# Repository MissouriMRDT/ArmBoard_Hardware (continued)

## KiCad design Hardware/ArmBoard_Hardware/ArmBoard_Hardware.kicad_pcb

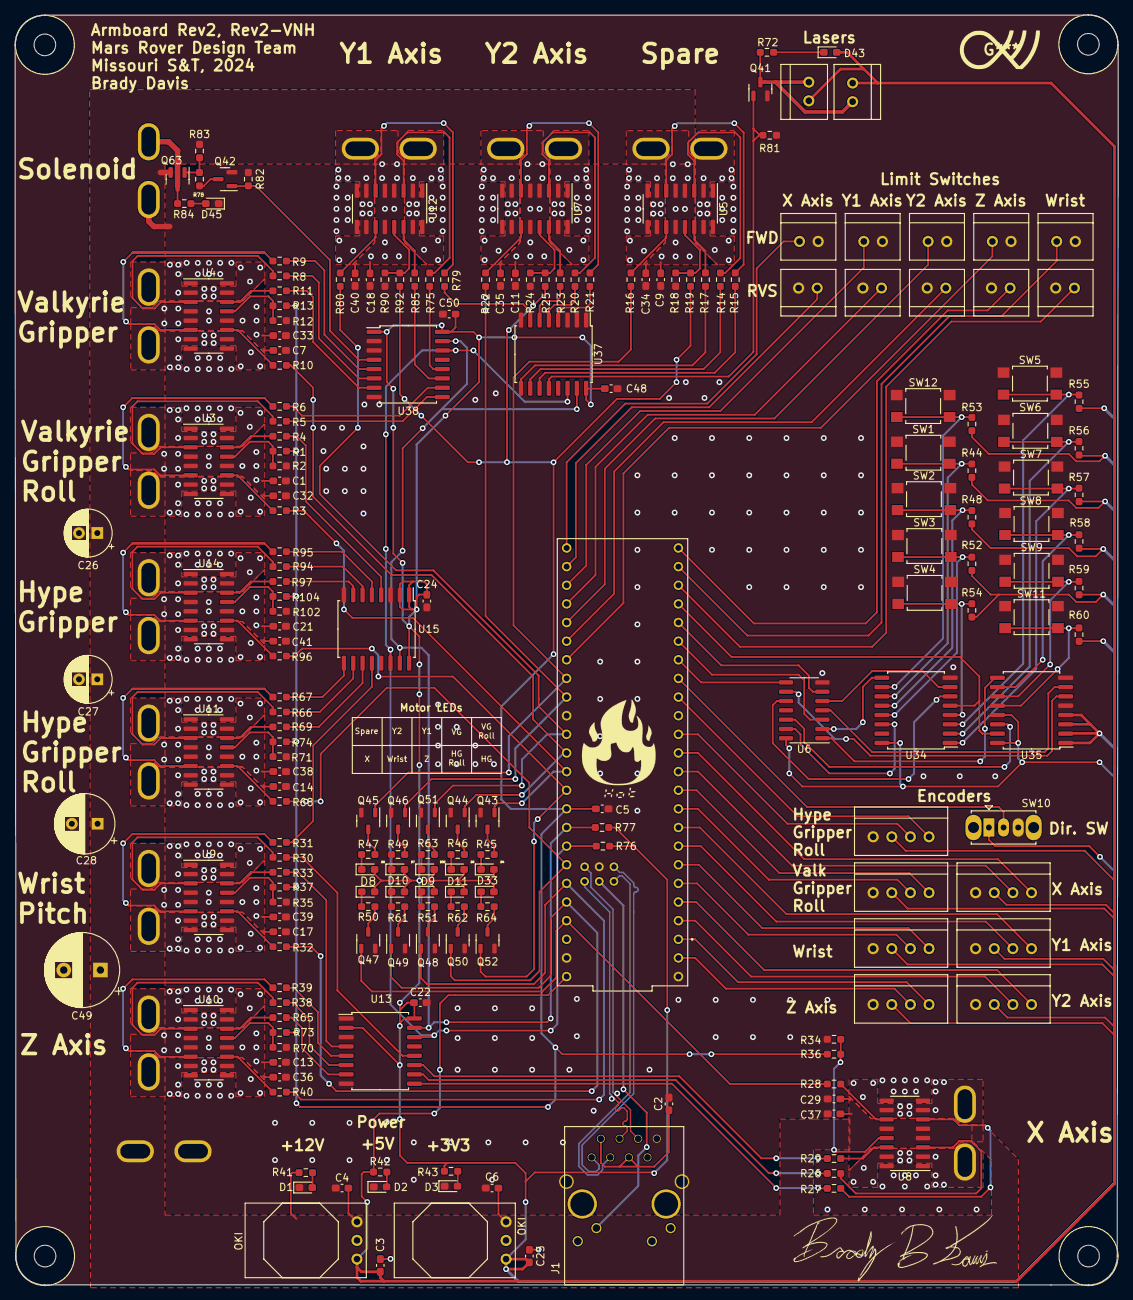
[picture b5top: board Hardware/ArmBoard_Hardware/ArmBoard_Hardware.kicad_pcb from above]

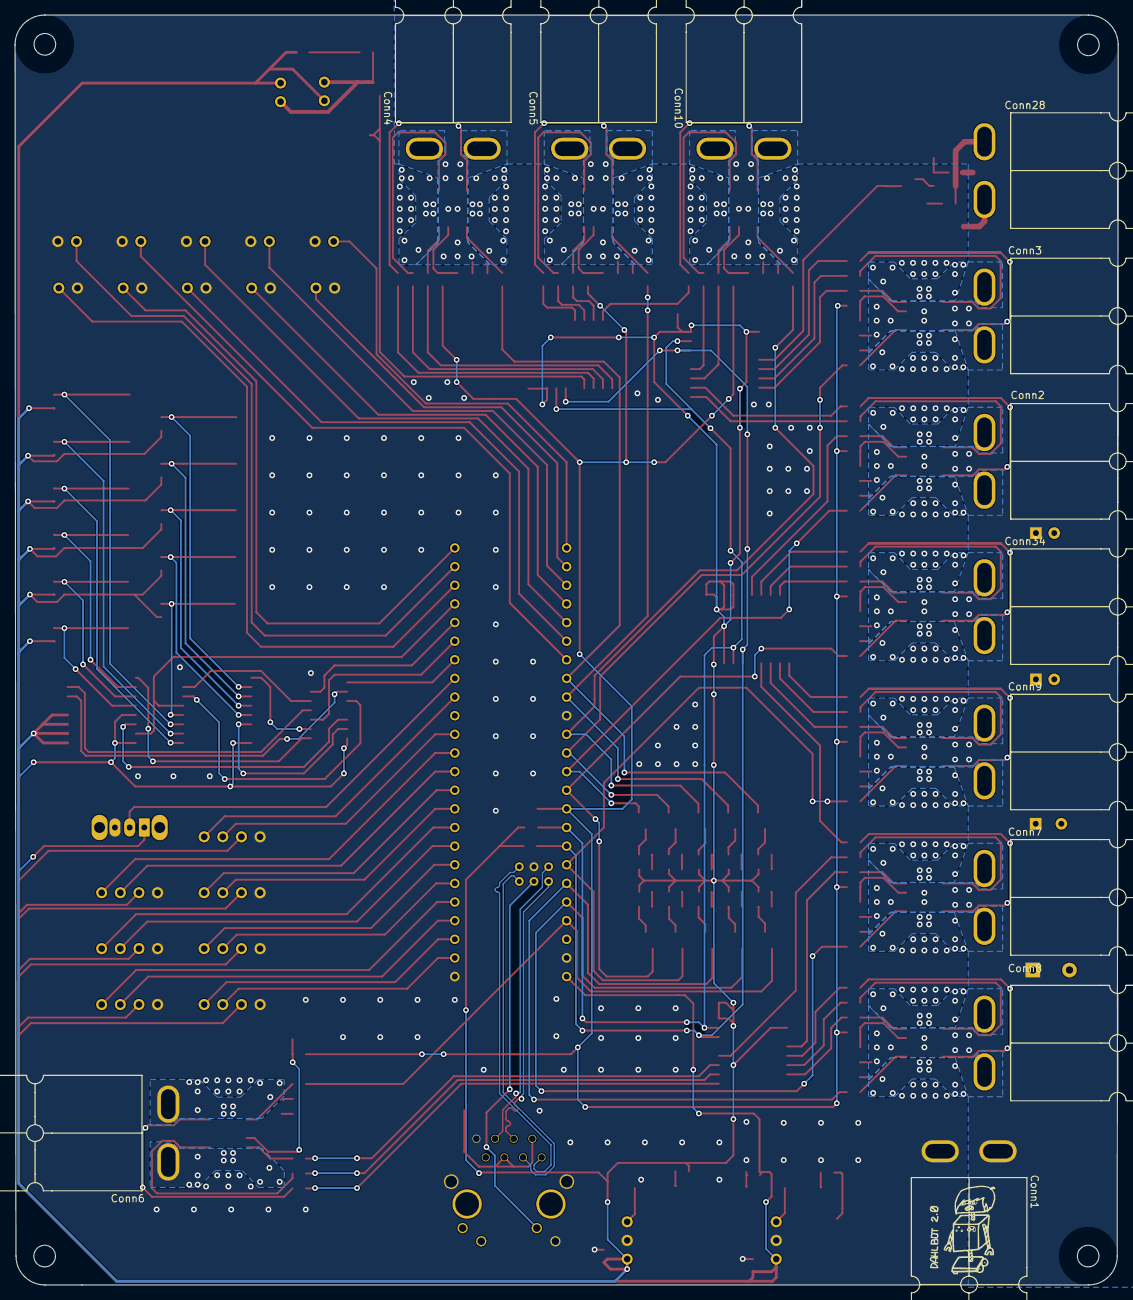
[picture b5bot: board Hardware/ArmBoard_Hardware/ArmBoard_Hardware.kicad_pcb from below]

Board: 2 copper layers, 150.4 x 173.1 mm, 222 parts (12 on the bottom side), 202 nets.

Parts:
C1, C2, C7, C9, C11, C13, C14, C17, C18, C21, C29: 0.1uF; C_0603_1608Metric_Pad1.08x0.95mm_HandSolder
C3, C4, C6, C25, C32, C34, C35, C36, C37, C38, C39, C40, C41: 10uF; C_0603_1608Metric_Pad1.08x0.95mm_HandSolder
C5: 10nF; C_0603_1608Metric_Pad1.08x0.95mm_HandSolder
C22, C24, C48, C50: 10 uF; C_0603_1608Metric_Pad1.08x0.95mm_HandSolder
C26: 100 uF; CP_Radial_D6.3mm_P2.50mm
C27: 220 uF; CP_Radial_D6.3mm_P2.50mm
C28: 330 uF; CP_Radial_D8.0mm_P3.50mm
C33: 100uF; C_0603_1608Metric_Pad1.08x0.95mm_HandSolder
C49: 470 uF; CP_Radial_D10.0mm_P5.00mm
Conn1, Conn2, Conn3, Conn4, Conn5, Conn6, Conn7, Conn8, Conn9, Conn10, Conn28, Conn34: AndersonPP; Square_Anderson_2_H_Side_By_Side
Conn11, Conn12, Conn13, Conn14, Conn15, Conn31, Conn32: Molex_SL_04; MOLEX_SL_04_Vertical
Conn17, Conn18, Conn19, Conn20, Conn21, Conn22, Conn23, Conn24, Conn25, Conn26, Conn29, Conn30: Molex_SL_02; MOLEX_SL_02_Vertical
D1, D2, D3: Green; LED_0603_1608Metric_Pad1.05x0.95mm_HandSolder
D4, D5, D6, D7, D8, D9, D10, D11, D32, D33: Blue; LED_0603_1608Metric_Pad1.05x0.95mm_HandSolder
D43, D45: Orange; LED_0603_1608Metric_Pad1.05x0.95mm_HandSolder
J1: RJ45_LED_Shielded; RJ45_Teensy
Q41, Q42: BSS138; SOT-23
Q43, Q44, Q45, Q46, Q47, Q48, Q49, Q50, Q51, Q52: T2N7002AK,LM; SOT-23-3
Q63: AO3401A; SOT-23
R1, R13, R19, R25, R36, R37, R73, R74, R78, R83, R92, R104: 10k; R_0603_1608Metric_Pad0.98x0.95mm_HandSolder
R2, R12, R18, R24, R34, R35, R43, R70, R71, R90, R102: 330; R_0603_1608Metric_Pad0.98x0.95mm_HandSolder
R3, R4, R5, R6, R8, R9, R10, R11, R14, R15, R16, R17, R20, R21, R22, R23, R26, R27, R28, R29, R30, R31, R32, R33, R38, R39, R40, R65, R66, R67, R68, R69, R75, R79, R80, R85, R94, R95, R96, R97: 1k; R_0603_1608Metric_Pad0.98x0.95mm_HandSolder
R41, R84: 2.2k; R_0603_1608Metric_Pad0.98x0.95mm_HandSolder
R42, R72: 620; R_0603_1608Metric_Pad0.98x0.95mm_HandSolder
R44, R48, R52, R53, R54, R55, R56, R57, R58, R59, R60, R76, R77, R81, R82: 4.7k; R_0603_1608Metric_Pad0.98x0.95mm_HandSolder
R45, R46, R47, R49, R50, R51, R61, R62, R63, R64: 220; R_0603_1608Metric_Pad0.98x0.95mm_HandSolder
SW1, SW2, SW3, SW4, SW5, SW6, SW7, SW8, SW9, SW11, SW12: SW_Push; SW_SPST_TL3305A
SW10: SW_SPDT; SW_Slide_1P2T_CK_OS102011MS2Q
U1, U36: OKI; OKI_Horizontal
U2: Teensy4.1_DEV-16771; Teensy_4_1_Ethernet
U3, U4, U5, U7, U8, U9, U10, U11, U12, U14: VNH7070AS; SOIC-16_3.9x9.9mm_P1.27mm
U6: 74HC00; SO-14_3.9x8.65mm_P1.27mm
U13, U15, U37, U38: PCF8574; SOIC-16W_7.5x10.3mm_P1.27mm
U34, U35: 74LS148; SOIC-16W_7.5x10.3mm_P1.27mm
V1, V2, V3, V4: Via; 4_40_Hole

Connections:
+3V3: C22.1, C24.1, C25.1, C48.1, C50.1, D4.2 (A), D5.2 (A), D6.2 (A), D7.2 (A), D8.2 (A), D9.2 (A), D10.2 (A), D11.2 (A), D32.2 (A), D33.2 (A), R43.1, R44.1, R48.1, R52.1, R53.1, R54.1, R55.1, R56.1, R57.1, R58.1, R59.1, R60.1, R76.1, R77.1, SW10.1 (A), U6.14 (VCC), U13.2 (A1), U13.16 (VDD), U15.1 (A0), U15.2 (A1), U15.16 (VDD), U34.16 (VCC), U35.1 (I4), U35.2 (I5), U35.3 (I6), U35.4 (I7), U35.13 (I3), U35.16 (VCC), U36.3 (Vo), U37.16 (VDD), U38.1 (A0), U38.16 (VDD)
+5V: C3.1, Conn11.2, Conn12.2, Conn13.2, Conn14.2, Conn15.2, Conn25.1, Conn26.1, Conn31.2, Conn32.2, D43.2 (A), R42.1, U1.3 (Vo), U2.VIN
+12V: C1.2, C4.1, C6.1, C7.2, C9.2, C11.2, C13.2, C14.2, C17.2, C18.2, C21.2, C26.1, C27.1, C28.1, C29.2, C32.2, C33.2, C34.2, C35.2, C36.2, C37.2, C38.2, C39.2, C40.2, C41.2, C49.1, Conn1.2 (V+Log), Q63.2 (S), R41.1, R83.1, U1.1 (Vi), U3.4 (VCC), U3.5 (VCC), U3.12 (VCC), U4.4 (VCC), U4.5 (VCC), U4.12 (VCC), U5.4 (VCC), U5.5 (VCC), U5.12 (VCC), U7.4 (VCC), U7.5 (VCC), U7.12 (VCC), U8.4 (VCC), U8.5 (VCC), U8.12 (VCC), U9.4 (VCC), U9.5 (VCC), U9.12 (VCC), U10.4 (VCC), U10.5 (VCC), U10.12 (VCC), U11.4 (VCC), U11.5 (VCC), U11.12 (VCC), U12.4 (VCC), U12.5 (VCC), U12.12 (VCC), U14.4 (VCC), U14.5 (VCC), U14.12 (VCC), U36.1 (Vi)
/M1+: Conn2.2 (V+Log), U3.2 (OUT_A), U3.15 (OUT_A)
/M1-: Conn2.1 (GND), U3.7 (OUT_B), U3.10 (OUT_B)
/M2+: Conn3.2 (V+Log), U4.2 (OUT_A), U4.15 (OUT_A)
/M2-: Conn3.1 (GND), U4.7 (OUT_B), U4.10 (OUT_B)
/M3+: Conn4.2 (V+Log), U5.2 (OUT_A), U5.15 (OUT_A)
/M3-: Conn4.1 (GND), U5.7 (OUT_B), U5.10 (OUT_B)
/M4+: Conn5.2 (V+Log), U7.2 (OUT_A), U7.15 (OUT_A)
/M4-: Conn5.1 (GND), U7.7 (OUT_B), U7.10 (OUT_B)
/M5+: Conn6.2 (V+Log), U8.2 (OUT_A), U8.15 (OUT_A)
/M5-: Conn6.1 (GND), U8.7 (OUT_B), U8.10 (OUT_B)
/M6+: Conn8.2 (V+Log), U10.2 (OUT_A), U10.15 (OUT_A)
/M6-: Conn8.1 (GND), U10.7 (OUT_B), U10.10 (OUT_B)
/M7+: Conn7.2 (V+Log), U9.2 (OUT_A), U9.15 (OUT_A)
/M7-: Conn7.1 (GND), U9.7 (OUT_B), U9.10 (OUT_B)
/M8+: Conn9.2 (V+Log), U11.2 (OUT_A), U11.15 (OUT_A)
/M8-: Conn9.1 (GND), U11.7 (OUT_B), U11.10 (OUT_B)
/M9+: Conn10.2 (V+Log), U12.2 (OUT_A), U12.15 (OUT_A)
/M9-: Conn10.1 (GND), U12.7 (OUT_B), U12.10 (OUT_B)
/M10+: Conn34.2 (V+Log), U14.2 (OUT_A), U14.15 (OUT_A)
/M10-: Conn34.1 (GND), U14.7 (OUT_B), U14.10 (OUT_B)
B_1: R53.2, SW12.2, U34.10 (IO)
B_2: R44.2, SW1.2, U34.11 (I1)
B_3: R48.2, SW2.2, U34.12 (I2)
B_4: R52.2, SW3.2, U34.13 (I3)
B_5: R54.2, SW4.2, U34.4 (I7)
B_6: R55.2, SW5.2, U34.3 (I6)
B_7: R56.2, SW6.2, U34.2 (I5)
B_8: R57.2, SW7.2, U34.1 (I4)
B_9: R58.2, SW8.2, U35.10 (IO)
B_10: R59.2, SW9.2, U35.11 (I1)
B_ENC_0: U2.27 (A13), U6.3
B_ENC_1: U2.28 (RX7), U6.6
B_ENC_2: U2.26 (A12), U6.8
B_ENC_3: U2.29 (TX7), U34.5 (EI), U35.15 (EO)
B_LAS: R60.2, SW11.2, U35.12 (I2)
CS: C5.1, R1.2, R13.2, R19.2, R25.2, R36.2, R37.2, R73.2, R74.2, R92.2, R104.2, U2.17 (A3)
DIR_SW: SW10.2 (B), U2.25 (A11)
EncoderA1: Conn12.3, U2.8 (TX2)
EncoderA2: Conn13.3, U2.10 (CS1)
EncoderA3: Conn14.3, U2.6 (OUT1D)
EncoderA4: Conn15.3, U2.4 (BCLK2)
EncoderA5: Conn31.3, U2.0 (RX1)
EncoderA6: Conn32.3, U2.2 (OUT2)
EncoderA7: Conn11.3, U2.12 (MISO)
EncoderB1: Conn12.4, U2.9 (OUT1C)
EncoderB2: Conn13.4, U2.11 (MOSI)
EncoderB3: Conn14.4, U2.7 (RX2)
EncoderB4: Conn15.4, U2.5 (IN2)
EncoderB5: Conn31.4, U2.1 (TX1)
EncoderB6: Conn32.4, U2.3 (LRCLK2)
EncoderB7: Conn11.4, U2.24 (A10)
GND: C1.1, C2.2, C3.2, C4.2, C5.2, C6.2, C7.1, C9.1, C11.1, C13.1, C14.1, C17.1, C18.1, C21.1, C22.2, C24.2, C25.2, C26.2, C27.2, C28.2, C29.1, C32.1, C33.1, C34.1, C35.1, C36.1, C37.1, C38.1, C39.1, C40.1, C41.1, C48.2, C49.2, C50.2, Conn1.1 (GND), Conn11.1, Conn12.1, Conn13.1, Conn14.1, Conn15.1, Conn17.2, Conn18.2, Conn19.2, Conn20.2, Conn21.2, Conn22.2, Conn23.2, Conn24.2, Conn28.1 (GND), Conn29.2, Conn30.2, Conn31.1, Conn32.1, D1.1 (K), D2.1 (K), D3.1 (K), D45.1 (K), J1.8, J1.9, J1.SH, Q41.2 (S), Q42.2 (S), Q43.2 (S), Q44.2 (S), Q45.2 (S), Q46.2 (S), Q47.2 (S), Q48.2 (S), Q49.2 (S), Q50.2 (S), Q51.2 (S), Q52.2 (S), R2.2, R12.2, R18.2, R24.2, R34.2, R35.2, R70.2, R71.2, R81.2, R82.2, R90.2, R102.2, SW1.1, SW2.1, SW3.1, SW4.1, SW5.1, SW6.1, SW7.1, SW8.1, SW9.1, SW10.3 (C), SW11.1, SW12.1, U1.2 (GND), U2.GND1 (GND), U2.GND2 (GND), U2.GND3 (GND), U2.GND5 (GND), U3.1 (GND_A), U3.8 (GND_B), U3.9 (GND_B), U3.16 (GND_A), U4.1 (GND_A), U4.8 (GND_B), U4.9 (GND_B), U4.16 (GND_A), U5.1 (GND_A), U5.8 (GND_B), U5.9 (GND_B), U5.16 (GND_A), U6.7 (GND), U7.1 (GND_A), U7.8 (GND_B), U7.9 (GND_B), U7.16 (GND_A), U8.1 (GND_A), U8.8 (GND_B), U8.9 (GND_B), U8.16 (GND_A), U9.1 (GND_A), U9.8 (GND_B), U9.9 (GND_B), U9.16 (GND_A), U10.1 (GND_A), U10.8 (GND_B), U10.9 (GND_B), U10.16 (GND_A), U11.1 (GND_A), U11.8 (GND_B), U11.9 (GND_B), U11.16 (GND_A), U12.1 (GND_A), U12.8 (GND_B), U12.9 (GND_B), U12.16 (GND_A), U13.1 (A0), U13.3 (A2), U13.8 (VSS), U14.1 (GND_A), U14.8 (GND_B), U14.9 (GND_B), U14.16 (GND_A), U15.3 (A2), U15.8 (VSS), U34.8 (GND), U35.5 (EI), U35.8 (GND), U36.2 (GND), U37.1 (A0), U37.2 (A1), U37.3 (A2), U37.8 (VSS), U38.2 (A1), U38.3 (A2), U38.8 (VSS)
IN_A1: R5.1, U38.9 (P4)
IN_A2: R8.1, U38.6 (P2)
IN_A3: R14.1, U37.10 (P5)
IN_A4: R20.1, U37.5 (P1)
IN_A5: R26.1, U13.10 (P5)
IN_A6: R38.1, U13.6 (P2)
IN_A7: R30.1, U13.12 (P7)
IN_A8: R66.1, U15.10 (P5)
IN_A9: R75.1, U38.12 (P7)
IN_A10: R94.1, U15.6 (P2)
IN_B1: R6.1, U38.10 (P5)
IN_B2: R9.1, U38.5 (P1)
IN_B3: R15.1, U37.11 (P6)
IN_B4: R21.1, U37.4 (P0)
IN_B5: R27.1, U13.9 (P4)
IN_B6: R39.1, U13.5 (P1)
IN_B7: R31.1, U15.12 (P7)
IN_B8: R67.1, U15.9 (P4)
IN_B9: R79.1, U37.7 (P3)
IN_B10: R95.1, U15.5 (P1)
LAS: Q41.1 (G), R81.1, U37.12 (P7)
LED: J1.10, U2.LED
LIM_1: Conn17.1, U2.33 (MCLK2)
LIM_2: Conn18.1, U2.34 (RX8)
LIM_3: Conn20.1, U2.35 (TX8)
LIM_4: Conn23.1, U2.36 (CS2)
LIM_5: Conn29.1, U2.31 (CTX3)
LIM_6: Conn21.1, U2.37 (CS3)
LIM_7: Conn19.1, U2.38 (A14)
LIM_8: Conn22.1, U2.39 (A15)
LIM_9: Conn24.1, U2.32 (OUT1B)
LIM_10: Conn30.1, U2.30 (CRX3)
unnamed: C2.1, J1.2, J1.5
unnamed: Conn28.2 (V+Log), Q63.3 (D), R84.1
unnamed: D1.2 (A), R41.2
unnamed: D2.2 (A), R42.2
unnamed: D3.2 (A), R43.2
unnamed: D4.1 (K), R45.1
unnamed: D5.1 (K), R46.1
unnamed: D6.1 (K), R47.1
unnamed: D7.1 (K), R49.1
unnamed: D8.1 (K), R50.1
unnamed: D9.1 (K), R51.1
unnamed: D10.1 (K), R61.1
unnamed: D11.1 (K), R62.1
unnamed: D32.1 (K), R63.1
unnamed: D33.1 (K), R64.1
unnamed: D43.1 (K), R72.1
unnamed: D45.2 (A), R84.2
unnamed: Conn25.2, Conn26.2, Q41.3 (D), R72.2
unnamed: Q42.3 (D), R78.2
unnamed: Q43.3 (D), R45.2
unnamed: Q44.3 (D), R46.2
unnamed: Q45.3 (D), R47.2
unnamed: Q46.3 (D), R49.2
unnamed: Q47.3 (D), R50.2
unnamed: Q48.3 (D), R51.2
unnamed: Q49.3 (D), R61.2
unnamed: Q50.3 (D), R62.2
unnamed: Q51.3 (D), R63.2
unnamed: Q52.3 (D), R64.2
unnamed: Q63.1 (G), R78.1, R83.2
unnamed: R1.1, R2.1, U3.13 (CS)
unnamed: R5.2, U3.3 (IN_A)
unnamed: R6.2, U3.6 (IN_B)
unnamed: R3.2, U3.11 (PWM)
unnamed: R4.2, U3.14 (SEL)
unnamed: R12.1, R13.1, U4.13 (CS)
unnamed: R8.2, U4.3 (IN_A)
unnamed: R9.2, U4.6 (IN_B)
unnamed: R10.2, U4.11 (PWM)
unnamed: R11.2, U4.14 (SEL)
unnamed: R18.1, R19.1, U5.13 (CS)
unnamed: R14.2, U5.3 (IN_A)
unnamed: R15.2, U5.6 (IN_B)
unnamed: R16.2, U5.11 (PWM)
unnamed: R17.2, U5.14 (SEL)
unnamed: R24.1, R25.1, U7.13 (CS)
unnamed: R20.2, U7.3 (IN_A)
unnamed: R21.2, U7.6 (IN_B)
unnamed: R22.2, U7.11 (PWM)
unnamed: R23.2, U7.14 (SEL)
unnamed: R34.1, R36.1, U8.13 (CS)
unnamed: R26.2, U8.3 (IN_A)
unnamed: R27.2, U8.6 (IN_B)
unnamed: R28.2, U8.11 (PWM)
unnamed: R29.2, U8.14 (SEL)
unnamed: R35.1, R37.1, U9.13 (CS)
unnamed: R30.2, U9.3 (IN_A)
unnamed: R31.2, U9.6 (IN_B)
unnamed: R32.2, U9.11 (PWM)
unnamed: R33.2, U9.14 (SEL)
unnamed: R70.1, R73.1, U10.13 (CS)
unnamed: R38.2, U10.3 (IN_A)
unnamed: R39.2, U10.6 (IN_B)
unnamed: R40.2, U10.11 (PWM)
unnamed: R65.2, U10.14 (SEL)
unnamed: R71.1, R74.1, U11.13 (CS)
unnamed: R66.2, U11.3 (IN_A)
unnamed: R67.2, U11.6 (IN_B)
unnamed: R68.2, U11.11 (PWM)
unnamed: R69.2, U11.14 (SEL)
unnamed: R90.1, R92.1, U12.13 (CS)
unnamed: R75.2, U12.3 (IN_A)
unnamed: R79.2, U12.6 (IN_B)
unnamed: R80.2, U12.11 (PWM)
unnamed: R85.2, U12.14 (SEL)
unnamed: R102.1, R104.1, U14.13 (CS)
unnamed: R94.2, U14.3 (IN_A)
unnamed: R95.2, U14.6 (IN_B)
unnamed: R96.2, U14.11 (PWM)
unnamed: R97.2, U14.14 (SEL)
unnamed: U6.13, U34.14 (GS)
unnamed: U6.2, U34.9 (S0)
unnamed: U6.5, U34.7 (S1)
unnamed: U6.10, U34.6 (S2)
unnamed: U6.12, U35.14 (GS)
unnamed: U6.1, U35.9 (S0)
unnamed: U6.4, U35.7 (S1)
unnamed: U6.9, U35.6 (S2)
PWM1: Q43.1 (G), R3.1, U2.15 (A1)
PWM2: Q44.1 (G), R10.1, U2.14 (A0)
PWM3: Q45.1 (G), R16.1, U2.40 (A16)
PWM4: Q46.1 (G), R22.1, U2.41 (A17)
PWM5: Q47.1 (G), R28.1, U2.23 (A9)
PWM6: Q48.1 (G), R40.1, U2.21 (A7)
PWM7: Q49.1 (G), R32.1, U2.22 (A8)
PWM8: Q50.1 (G), R68.1, U2.20 (A6)
PWM9: Q51.1 (G), R80.1, U2.13 (SCK)
PWM10: Q52.1 (G), R96.1, U2.16 (A2)
Rx+: J1.4, U2.R+
Rx-: J1.6, U2.R-
SCL: R76.2, U2.19 (A5), U13.14 (SCL), U15.14 (SCL), U37.14 (SCL), U38.14 (SCL)
SDA: R77.2, U2.18 (A4), U13.15 (SDA), U15.15 (SDA), U37.15 (SDA), U38.15 (SDA)
SEL1: R4.1, U15.4 (P0)
SEL2: R11.1, U38.7 (P3)
SEL3: R17.1, U37.9 (P4)
SEL4: R23.1, U37.6 (P2)
SEL5: R29.1, U13.11 (P6)
SEL6: R65.1, U13.7 (P3)
SEL7: R33.1, U13.4 (P0)
SEL8: R69.1, U15.11 (P6)
SEL9: R85.1, U38.11 (P6)
SEL10: R97.1, U15.7 (P3)
Solenoid: Q42.1 (G), R82.1, U38.4 (P0)
Tx+: J1.1, U2.T+
Tx-: J1.3, U2.T-

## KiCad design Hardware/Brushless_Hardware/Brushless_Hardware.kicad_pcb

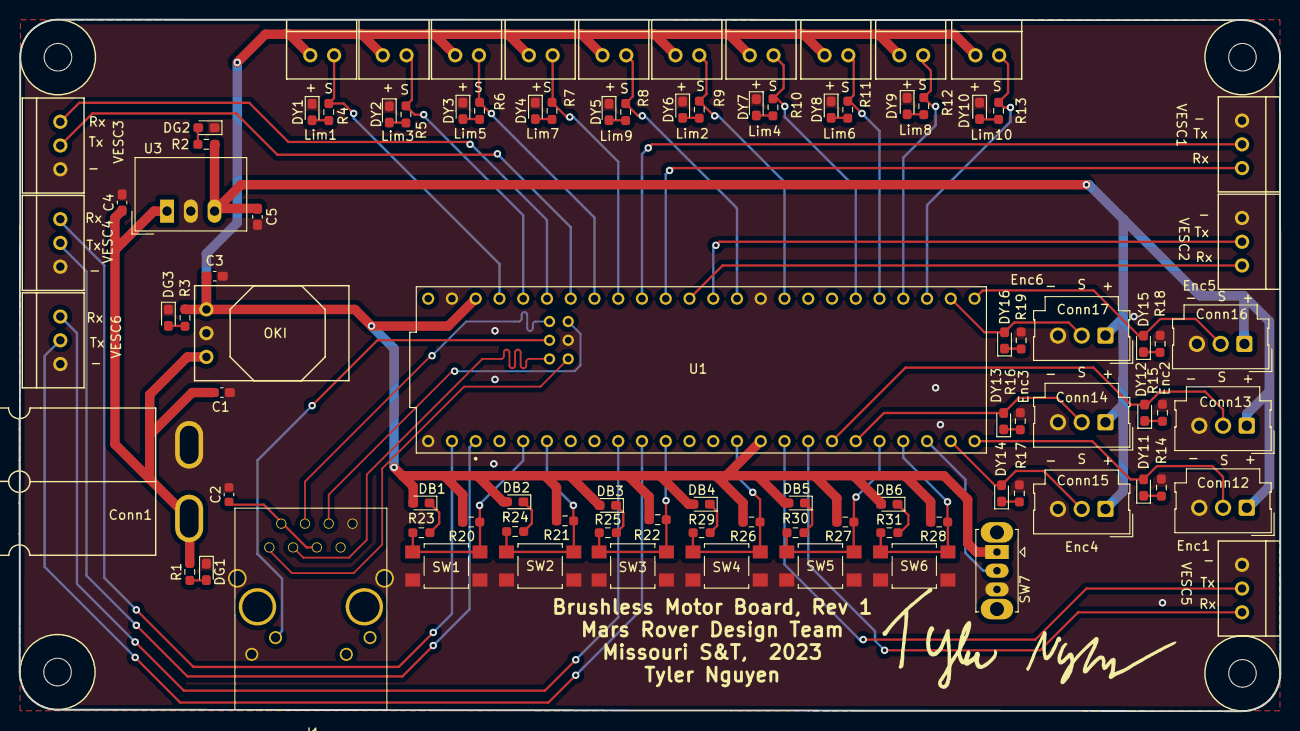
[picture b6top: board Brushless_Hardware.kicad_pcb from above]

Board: 2 copper layers, 134.8 x 73.9 mm, 99 parts (0 on the bottom side), 70 nets.

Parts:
C1, C3, C4, C5: 10 uF; C_0603_1608Metric_Pad1.08x0.95mm_HandSolder
C2: 0.1uF; C_0603_1608Metric
Conn1: AndersonPP; Square_Anderson_2_H_Side_By_Side_PV
Conn2, Conn3, Conn4, Conn5, Conn6, Conn7, Conn8, Conn9, Conn10, Conn11: Molex_SL_02; MOLEX_SL_02_Vertical
Conn12, Conn13, Conn14, Conn15, Conn16, Conn17: Molex_SL_03; Molex_SL_171971-0003_1x03_P2.54mm_Vertical
Conn18, Conn19, Conn20, Conn21, Conn22, Conn23: Molex_SL_03; MOLEX_SL_03_Vertical
DB1, DB2, DB3, DB4, DB5, DB6: Blue; LED_0603_1608Metric_Pad1.05x0.95mm_HandSolder
DG1, DG2, DG3: Green; LED_0603_1608Metric_Pad1.05x0.95mm_HandSolder
DY1, DY2, DY3, DY4, DY5, DY6, DY7, DY8, DY9, DY10, DY11, DY12, DY13, DY14, DY15, DY16: Yellow; LED_0603_1608Metric_Pad1.05x0.95mm_HandSolder
J1: RJ45_LED_Shielded; RJ45_Teensy
R1: 3000; R_0603_1608Metric_Pad0.98x0.95mm_HandSolder
R2, R14, R15, R16, R17, R18, R19: 300; R_0603_1608Metric_Pad0.98x0.95mm_HandSolder
R3, R4, R5, R6, R7, R8, R9, R10, R11, R12, R13: 100; R_0603_1608Metric_Pad0.98x0.95mm_HandSolder
R20, R21, R22, R26, R27, R28: 4.7k; R_0603_1608Metric_Pad0.98x0.95mm_HandSolder
R23, R24, R25, R29, R30, R31: 120; R_0603_1608Metric_Pad0.98x0.95mm_HandSolder
SW1, SW2, SW3, SW4, SW5, SW6: SW_Push; SW_SPST_TL3305A
SW7: SW_DPDT_x2; SW_Slide_1P2T_CK_OS102011MS2Q
U1: Teensy4.1_DEV-16771; Teensy_4_1_Ethernet
U2: OKI; OKI_Horizontal
U3: TSR_1-2450; Converter_DCDC_TRACO_TSR-1_THT
V1, V2, V3, V4: Via; 4_40_Hole_Corner

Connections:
+3.3V: C3.2, Conn2.1, Conn3.1, Conn4.1, Conn5.1, Conn6.1, Conn7.1, Conn8.1, Conn9.1, Conn10.1, Conn11.1, DB1.2 (A), DB2.2 (A), DB3.2 (A), DB4.2 (A), DB5.2 (A), DB6.2 (A), R3.2, R20.1, R21.1, R22.1, R26.1, R27.1, R28.1, SW7.1 (A), U1.3.3V_1 (3.3V), U1.3.3V_2 (3.3V), U2.3 (Vo)
+5V: C5.2, Conn12.1, Conn13.1, Conn14.1, Conn15.1, Conn16.1, Conn17.1, R2.2, U3.3 (Vout)
+36V: C1.1, C4.1, Conn1.4 (PV+), R1.2, U2.1 (Vi), U3.1 (Vin)
B1: R20.2, R23.2, SW1.2, U1.3 (LRCLK2)
B2: R21.2, R24.2, SW2.2, U1.4 (BCLK2)
B3: R22.2, R25.2, SW3.2, U1.9 (OUT1C)
B4: R26.2, R29.2, SW4.2, U1.12 (MISO)
B5: R27.2, R30.2, SW5.2, U1.28 (RX7)
B6: R28.2, R31.2, SW6.2, U1.29 (TX7)
ENC_1: Conn12.2, DY11.2 (A), U1.32 (OUT1B)
ENC_2: Conn13.2, DY12.2 (A), U1.26 (A12)
ENC_3: Conn14.2, DY13.2 (A), U1.27 (A13)
ENC_4: Conn15.2, DY14.2 (A), U1.31 (CTX3)
ENC_5: Conn16.2, DY15.2 (A), U1.33 (MCLK2)
ENC_6: Conn17.2, DY16.2 (A), U1.34 (RX8)
GND: C1.2, C2.2, C3.1, C4.2, C5.1, Conn1.1 (GND), Conn12.3, Conn13.3, Conn14.3, Conn15.3, Conn16.3, Conn17.3, Conn18.1, Conn19.1, Conn20.1, Conn21.1, Conn22.1, Conn23.1, DG1.1 (K), DG2.1 (K), DG3.1 (K), DY1.1 (K), DY2.1 (K), DY3.1 (K), DY4.1 (K), DY5.1 (K), DY6.1 (K), DY7.1 (K), DY8.1 (K), DY9.1 (K), DY10.1 (K), J1.8, J1.9, J1.SH, R14.2, R15.2, R16.2, R17.2, R18.2, R19.2, SW1.1, SW2.1, SW3.1, SW4.1, SW5.1, SW6.1, SW7.3 (C), U1.GND1 (GND), U1.GND2 (GND), U1.GND3 (GND), U1.GND5 (GND), U2.2 (GND), U3.2 (GND)
LED: J1.10, U1.LED
LIM_1: Conn2.2, R4.1, U1.23 (A9)
LIM_2: Conn7.2, R9.1, U1.41 (A17)
LIM_3: Conn3.2, R5.1, U1.22 (A8)
LIM_4: Conn8.2, R10.1, U1.38 (A14)
LIM_5: Conn4.2, R6.1, U1.19 (A5)
LIM_6: Conn9.2, R11.1, U1.37 (CS3)
LIM_7: Conn5.2, R7.1, U1.18 (A4)
LIM_8: Conn10.2, R12.1, U1.36 (CS2)
LIM_9: Conn6.2, R8.1, U1.13 (SCK)
LIM_10: Conn11.2, R13.1, U1.35 (TX8)
unnamed: C2.1, J1.2, J1.5
unnamed: DB1.1 (K), R23.1
unnamed: DB2.1 (K), R24.1
unnamed: DB3.1 (K), R25.1
unnamed: DB4.1 (K), R29.1
unnamed: DB5.1 (K), R30.1
unnamed: DB6.1 (K), R31.1
unnamed: DG1.2 (A), R1.1
unnamed: DG2.2 (A), R2.1
unnamed: DG3.2 (A), R3.1
unnamed: DY1.2 (A), R4.2
unnamed: DY2.2 (A), R5.2
unnamed: DY3.2 (A), R6.2
unnamed: DY4.2 (A), R7.2
unnamed: DY5.2 (A), R8.2
unnamed: DY6.2 (A), R9.2
unnamed: DY7.2 (A), R10.2
unnamed: DY8.2 (A), R11.2
unnamed: DY9.2 (A), R12.2
unnamed: DY10.2 (A), R13.2
unnamed: DY11.1 (K), R14.1
unnamed: DY12.1 (K), R15.1
unnamed: DY13.1 (K), R16.1
unnamed: DY14.1 (K), R17.1
unnamed: DY15.1 (K), R18.1
unnamed: DY16.1 (K), R19.1
Rx+: J1.4, U1.R+
Rx-: J1.6, U1.R-
SW: SW7.2 (B), U1.30 (CRX3)
Tx+: J1.1, U1.T+
Tx-: J1.3, U1.T-
VESC_Rx_1: Conn18.3, U1.16 (A2)
VESC_Rx_2: Conn19.3, U1.15 (A1)
VESC_Rx_3: Conn20.3, U1.21 (A7)
VESC_Rx_4: Conn21.3, U1.0 (RX1)
VESC_Rx_5: Conn22.3, U1.25 (A11)
VESC_Rx_6: Conn23.3, U1.7 (RX2)
VESC_Tx_1: Conn18.2, U1.17 (A3)
VESC_Tx_2: Conn19.2, U1.14 (A0)
VESC_Tx_3: Conn20.2, U1.20 (A6)
VESC_Tx_4: Conn21.2, U1.1 (TX1)
VESC_Tx_5: Conn22.2, U1.24 (A10)
VESC_Tx_6: Conn23.2, U1.8 (TX2)

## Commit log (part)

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2019-11-21 Added Silks, 100% done
2019-11-21 eat a bagel
2019-12-05 Frick me, my B
2019-12-06 Reducing Electrical Leads bitching potential
2019-12-07 Hurt me daddy
2019-12-07 Suck my toes
2020-01-21 Created Step FIle
2020-02-06 3 up, three down, suck my toes
2020-02-26 Generated Gerbs
2020-08-24 Renaming things for documentation
2021-10-01 Init Commit
    Removed old files. Added new project, reference docs,
2021-10-02 Moved everything to a new format. Instead of using global lables I used hierarchical so it would look better. needs to be double checked. check and make sure we dont have any unused schematic files
2021-10-15 Pwms have been routed to Pwm Pins. and I added the laser and solenoid mosfets and connectors
2021-10-16 made the main sch smaller
2021-10-16 moved text
2021-10-16 wire fix
2021-10-16 Pin Assignments
2021-10-16 Updated Numbering and BOM
2021-10-21 Added Schematics
2021-11-08 need to change the mosfet and the other footrpints under it
2021-11-10 Updated Symbols
    Fixed orientation of Led Fets, removed Fets for fault detection indicators to minimize components
2021-11-10 beginning layout, need to double check footprints and create BOM
2021-11-12 layout
2021-11-16 week 2 of layout. andersons fixed and are in correct direction for now. moved VNHs up. plan to put tiva on back of board.
2021-11-16 extended board by 0.5in to height
2021-11-16 components over top of moco VNHs
2021-11-17 yeet
2021-11-17 yeet2
2021-11-17 late night with the boy
2021-11-20 Fixed Oscillators
2021-11-24 Worked on Motor Drivers
    added major tracing of motor drivers
2021-11-24 Power Rails and LEDs
    Routed Power and Power Indicators, starting to route signals
2021-11-27 Routed Major Signals
2021-11-27 All Routing Done
    Ran DRC with all checking options, fixed any errors
2021-12-01 armboard review
2021-12-02 Removed all signal routing
    Whelp it's gonna look better by tonight
2021-12-02 Updated Footprints
2021-12-02 LEDs routed, footprints correctly assigned
2021-12-03 Rerouted all traces
2021-12-03 silk screen rev1
2021-12-04 Replaced Fets
2021-12-08 generated gerbs and step files
2021-12-31 Rescued the Libaries
2021-12-31 removed rescue library dcm file
2022-01-27 Test Commit
    M1 Vref to gnd trace deleted
2022-02-08 project library cleanup - deleted unused and moved them to one folder
2022-02-09 consept pcb
2022-02-11 Rev 2, still needs new mosfet circuit and new solenoid mosfet tthat can handle it
2022-02-12 minor changes
2022-02-12 bad via on 12va fixed
2022-02-12 get rid of 5v led
2022-02-12 visual improvements
2022-02-15 added limit switches to a total of 6
2022-02-16 cleanup
2022-02-22 Started Changes
    Via spacing and density
2022-02-22 Fixed edge cuts
2022-02-22 Made size smaller
2022-02-22 need to change encoder traces, need to add ground resistors to the vnh's and the led trace needs to be redone
2022-02-26 save before runs
2022-02-26 rev 2 finishing passes
2022-03-03 minor changes, changed the vnh traces
2022-03-05 more changes, realignment of alot of stuff
2022-03-07 moved the andersons
2022-03-07 moved traces
2022-03-08 trace cleanup
2022-03-09 Board Review
2022-03-10 final
2022-03-12 updated BOM
2022-03-15 gerbs added and zipped
2022-03-15 final gerbs
2022-03-16 added names and labeling
2022-04-06 Generated step file
2022-05-07 rev 2.1 updated with new pwm pin from PM2 to Motor1 PWM1 instead of PH3
2022-09-10 Initial design of h-bridge prototype
2022-09-14 Deleted unnecessary autosave file
2022-09-14 The whole gosh dang schematic
2022-09-14 Actually Saved this time
2022-09-19 PDR changes to top h-bridge
2022-09-19 Flipped input and output tags on limit switches, encoders, and laser
2022-09-20 PDR Changes to H-Bridge and Layout
2022-09-20 The Anderson Silkscreens were being annoying so i got rid of them
2022-09-20 Picked a diode for the h-bridge itll work probably idk im tired
2022-10-12 Initial PCB Layout with Revised H-Bridges
2022-10-12 Created extra laser, assigned distinct labels for each h-bridge, updated footprint assignment, updated PCB layout
2022-10-17 Optimizing layout spacing, added silkscreen annotations
2022-10-20 Cleaned up some of the ground plane gaps, various minor changes
2022-10-29 Rearranged Stuff so the ground plane flows nicer
2022-10-31 Added Malacki signature
2022-11-12 Added Inverters to H-Bridges, started Teensy Schematic
2022-11-16 Assigned Teensy pins and added RJ45 port
2022-11-16 Started layout
2022-11-17 Connected inverters
2022-11-17 Changed h-bridge capacitor values
2022-11-17 Cleaned up traces. Reduced overall circuit board footprint
2022-12-21 Enlarged 12V Plane, reran traces for ground continuity
2022-12-23 Started rearranging layout for horizontal teensy
2022-12-29 Board Shrink + Rerout + Pin Reassignment
2022-12-29 Added Ezekiel Allen signature
2023-02-09 Added 6 limit switches
2023-02-09 Added Zeke Signature
2023-03-13 Add buttons and 16:4 priority encoder
2023-03-13 Completed schematic
    Combined laser toggles to save pin space on Teensy. Adjusted buttons from SPDT to SPST with pull-up resistors, to match standard.
2023-03-16 Started routing traces
2023-03-17 More trace work
2023-03-21 Post board review changes
2023-03-21 generated gerbs and cleaned up files
2023-04-11 Fixed incorrect capacitor value
2023-04-12 Added 6 encoders ands 10 limit switches
2023-04-18 Added buttons and connectors for vesc
2023-04-19 Added direction switch and connectors
2023-04-19 Added flags to teensy
2023-04-19 updated teensy to include encoder and limit switches flags
2023-04-20 fixed flags and started PCB
2023-04-20 organized components
2023-04-21 started powerline
2023-04-21 started doing traces
2023-04-21 worked on fixing the board for a bit
2023-04-22 fixed placement and redid board
2023-04-22 Fixed labeling again
2023-05-06 Made STEP file
2023-09-24 Ready for schematic reviews (not)
2023-09-24 Post schematic review
2023-09-28 Changed Anderson to V+ Log instead of V+ Act
2023-10-15 layout spaced components
2023-10-16 some layout review changes
2023-10-31 layout review 2
2023-11-01 final layout for orders
2023-11-05 fourth layout review fixes
2023-11-13 gerbs generated
2024-03-21 Started on ArmBoardRev2
    Laid out general components
2024-03-22 Added RJ45 port and buttons
2024-03-22 Fixed LED
2024-03-22 Finished teensy
2024-03-23 Organized Schematic Layout
    I added changes such as moving things around, separating circuits with lines, and creating titles for each circuit to make it easier to read
2024-03-30 Brady's board rev 3/29
2024-03-30 Updated cap values on oki circuits
2024-04-05 Finishes schematic and applied footprints
2024-04-06 Creation of VNH Rev 2 Board
    Creation of VNH Rev 2 Board created by Sean Duda
2024-04-06 Completed Footprint Assignment
    Completed Footprint Assignment
2024-04-06 Finished andersons
2024-04-06 Placed Components and Made Power Planes
    Placed Components for trace routing, and made power planes for motors and 12V
2024-04-06 Buttons finished
2024-04-07 Teensy traces
2024-04-07 Edited power planes for VNH and routed traces
    Routed signal traces and edited power planes for VNH chip to fit 12V pads
2024-04-08 Layout finished before review
    Added 3v3 and 5V lines
    Need vias for planes
2024-04-08 Reworked Traces to match Arm Board size restraints
    Reworked traces and power planes to meet size and power requirements for the VNH chip, and the size calculations for the new Arm Board Mount
2024-04-08 Fixed missing traces
2024-04-09 Ran traces for ICs
    Ran traces for ICs and connectors to finish the routing on Arm. (Vias needed)
2024-04-09 Placed Vias for 12V plane and reworked traces
    Placed vias for 12V and reworked traces by giving more space from pads on ICs
2024-04-09 Fixed some things on review
2024-04-09 Fixed more things from review notes
    -SW10 3V3 trace routing
    -Fixed 12V trace on solenoid
    -Moved bottom right moco to give room to mounting hole
2024-04-09 Fixed M+/M-
    -Still need to fix capacitor bank locations
2024-04-09 Routed traces for switches and limit switches
    Routed traces for switches, buttons, limit switches, and binary encoders
2024-04-09 Routed traces and tweaked power planes
    Routed traces for IO expanders and tweaked 12V power planes
2024-04-10 Fixed labels on IO extenders
2024-04-10 Removed 12V Power plane, and traces
    Removed 12V power plane, and traces. Moved Anderson's for easier 12V plane connection
2024-04-10 layed out most of moco circuits
2024-04-11 Added Will Face, Adjusted Vias, 12V plane extend to right andy
2024-04-11 placed all components, some routing done; should be mostly connect the dots at this point
2024-04-11 Fixed
    -12V plane cutting off ground
    -sharp corners on traces
    -Changed button labels
2024-04-12 Fix 12V and motor output plane overlap
2024-04-12 finished layout
2024-04-13 Fixed ground plane to through hole caps
2024-04-13 Fixed 5V traces from oki to SLs
2024-09-23 Added KiCAD files
2024-09-27 Placed Components
    Boom
2024-09-29 Encoder/Decoders
2024-10-02 Added teensy labels
2024-10-04 Edits made in Moco SIgnals
2024-10-05 Changes made
    Deleted extra wire
2024-10-05 removed extra files
2024-10-10 psuh
2024-10-16 Grounded standby on CAN transceiver
2024-10-18 update footprints
2024-10-21 Edit on PCB and footprints
    Please pop up this time
2024-10-21 Fixed Footprint assignments
2024-10-22 Layout updated
2024-10-23 schematic update
2024-10-24 Layout editted
2024-10-24 Referred to past layouts
2024-10-27 Revert "Made Gerbs"
    This reverts commit e8fd2e3e654022122d892e8da1e72b2455c4286f.
2024-10-27 Revert "gerbs"
    This reverts commit 07dacdaaa2a46f5aa43cc62f0396f5798a40864e.
2024-10-28 Grouped switches done
    Still doing for signals and encoders
2024-10-29 Layout arrangement done, traces connected on OKIs
    Not finalized but will get back to change the arrangement of SL if needed
2024-11-01 Adjusted mosfet connections, previously was wrong
2024-11-02 Progress to get board dimensions
2024-11-02 Passed DRC and added diff pair
2024-11-05 Removed blue traces to make new layout arrangement
2024-11-07 Removed red traces to rearrange components
2024-11-07 Removed traces
2024-11-11 Jesse bitchin
2024-11-11 changes after board grilling
2024-11-12 Double check to see changes were fully pushed into Github
2024-11-18 LEDs compacted more to OKIs, SL connection adjusted (might need to redo), IO expanders position changed
2025-09-06 Inital commit
2025-09-12 Added workflow
2025-10-03 Power Sheet Started :3
2025-10-05 CAN Sheet Started w/ Hierarchical Labels :D
2025-10-06 Added Buttons/Ethernet
    Added 14 buttons a direction switch and a ethernet port
2025-10-06 Fixing push ?
2025-10-06 Revert "Added Buttons/Ethernet"
    This reverts commit 9980516216efd01912de7bddb560febaf0714407.
2025-10-06 Fix gitignore
2025-10-07 Buttons UwU
    Placed 14 buttons and a direction switch.
2025-10-07 Changing CRX and CTX Round 2 :((
2025-10-07 Added Servos
    Added servo molexs
2025-10-10 Added root pins
    Root beer
2025-10-10 Final 1
2025-10-14 Fixed ground
    fixed ground in MCU and added no connect flags.
2025-10-22 Schematic review changes part 2 the electric boogaloo
    finished fixing schematic. Made better names for heiracal pins. Made LED ressistors standard values.
2025-10-23 Prototype Layout
    Made an initial Layout to be edited and changed uwu
2025-10-29 Added Labels/ fixed edge
    Added labels to molexs and fixed board cut out
2025-10-30 Began Traces and shrunk board complete redesign
    Complete3ly redid the board to be smaller and make traces
2025-10-31 signal matchinfg
2025-10-31 Traces done needs to be lengthened slightly
    traces should be good but board needs to be a tad bit longer for labels and possible components in the future
2025-11-10 Minor fixes
2025-11-11 Fixed Labels, Molex, Added silkscreen
2025-11-13 Labeled Laser LED
    Labeles yippie
2025-11-16 Fix reverse voltage protection circuit
2025-11-17 Fix DRC Errors
2025-11-17 Fixed silkscreen
2025-11-17 Fixed power plane
2025-11-17 Shift around diode a lil bit
2026-03-18 Rev 2 start
    Fixed schematic for Rev 2, needs layout changes see sharepoint
2026-03-19 Changed silkscreens and positions of components for Rev2 + Schematic
2026-03-20 SilkScreen
    Added Silkscreen
2026-03-20 Add soldermask remove and plated holes
